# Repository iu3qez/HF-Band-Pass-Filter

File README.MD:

Preliminary version, please do not use.

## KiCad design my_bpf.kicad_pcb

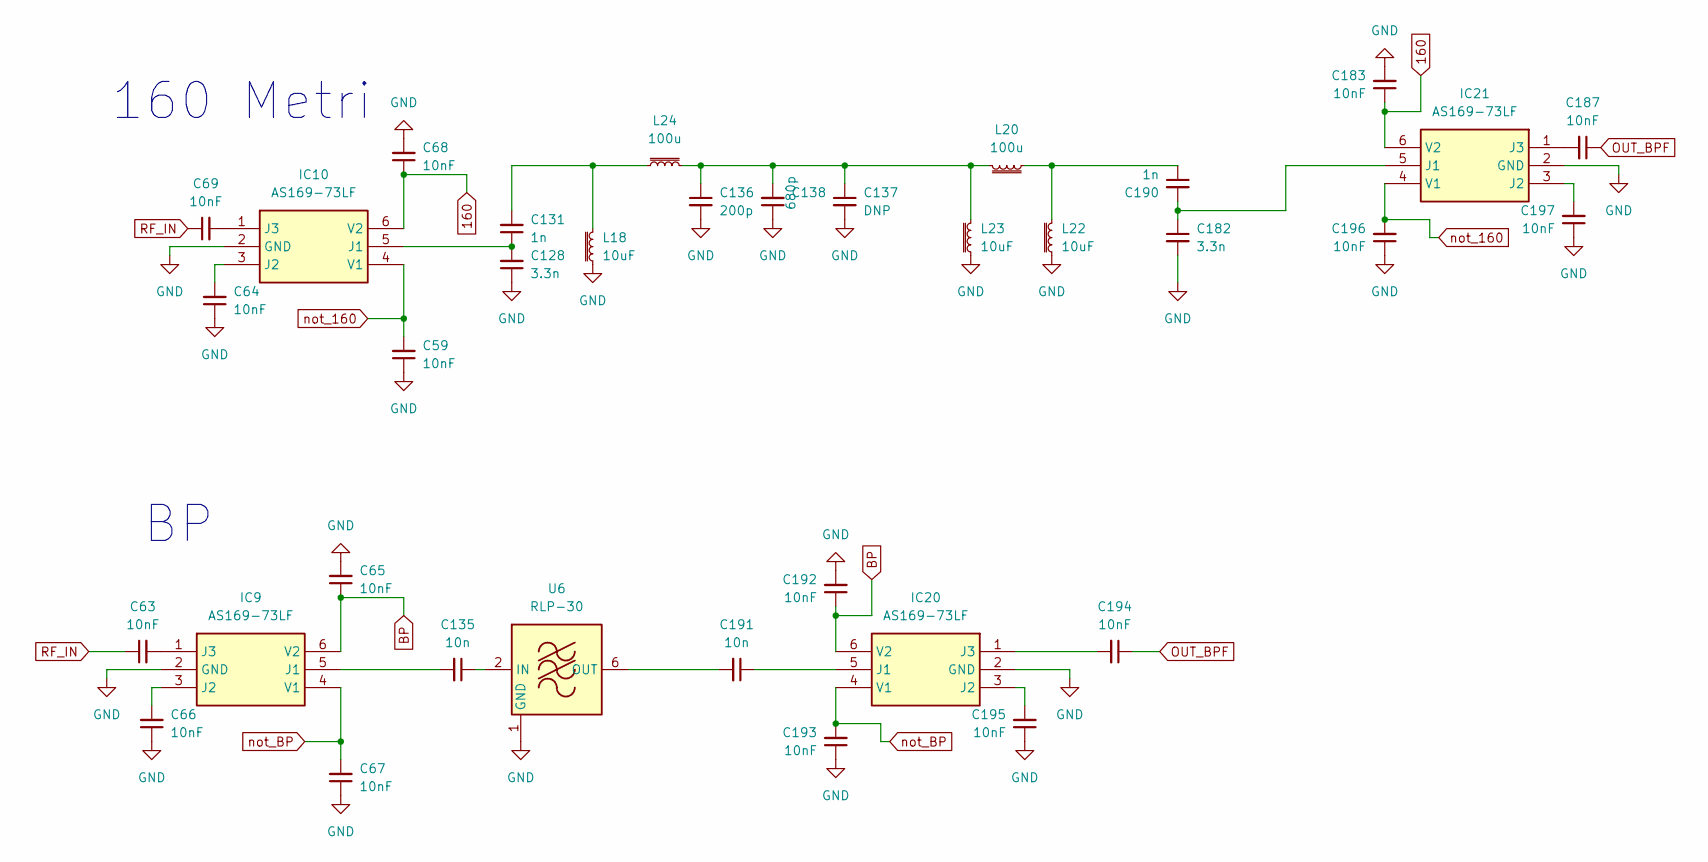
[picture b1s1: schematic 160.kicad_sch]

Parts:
C59, C63, C64, C65, C66, C67, C68, C69, C183, C187, C192, C193, C194, C195, C196, C197: 10nF; C_0603_1608Metric_Pad1.08x0.95mm_HandSolder
C128, C182: 3.3n; C_0603_1608Metric_Pad1.08x0.95mm_HandSolder
C131, C190: 1n; C_0603_1608Metric_Pad1.08x0.95mm_HandSolder
C135, C191: 10n; C_0603_1608Metric_Pad1.08x0.95mm_HandSolder
C136: 200p; C_0603_1608Metric_Pad1.08x0.95mm_HandSolder
C137: DNP; C_0603_1608Metric_Pad1.08x0.95mm_HandSolder
C138: 680p; C_0603_1608Metric_Pad1.08x0.95mm_HandSolder
IC9, IC10, IC20, IC21: AS169-73LF; SOT95P270X145-6N; Mouser Part Number 873-AS169-73LF
L18, L22, L23: 10uF; T37
L20, L24: 100u; T37
U6: RLP-30; Mini-Circuits_GP1212_LandPatternPL-176

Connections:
160: C68.1, C183.1, IC10.6 (V2), IC21.6 (V2); also elsewhere on the board
BP: C65.1, C192.1, IC9.6 (V2), IC20.6 (V2); also elsewhere on the board
GND: C59.1, C64.1, C65.2, C66.1, C67.1, C68.2, C128.1, C136.2, C137.2, C138.1, C182.2, C183.2, C192.2, C193.1, C195.1, C196.1, C197.1, IC9.2 (GND), IC10.2 (GND), IC20.2 (GND), IC21.2 (GND), L18.1, L22.1, L23.1, U6.1 (GND), U6.3 (GND), U6.4 (GND), U6.5 (GND), U6.7 (GND), U6.8 (GND); also elsewhere on the board
IN_BPF: C63.1, C69.1; also elsewhere on the board
unnamed: C131.2, L18.2, L24.1
unnamed: C136.1, C137.1, C138.2, L20.2, L23.2, L24.2
unnamed: C190.1, L20.1, L22.2
unnamed: C135.2, IC9.5 (J1)
unnamed: C66.2, IC9.3 (J2)
unnamed: C63.2, IC9.1 (J3)
unnamed: C128.2, C131.1, IC10.5 (J1)
unnamed: C64.2, IC10.3 (J2)
unnamed: C69.2, IC10.1 (J3)
unnamed: C191.1, IC20.5 (J1)
unnamed: C195.2, IC20.3 (J2)
unnamed: C194.2, IC20.1 (J3)
unnamed: C182.1, C190.2, IC21.5 (J1)
unnamed: C197.2, IC21.3 (J2)
unnamed: C187.2, IC21.1 (J3)
unnamed: C135.1, U6.2 (IN)
unnamed: C191.2, U6.6 (OUT)
OUT_BPF: C187.1, C194.1; also elsewhere on the board
not_160: C59.2, C196.2, IC10.4 (V1), IC21.4 (V1); also elsewhere on the board
not_BP: C67.2, C193.2, IC9.4 (V1), IC20.4 (V1); also elsewhere on the board

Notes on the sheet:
160 Metri

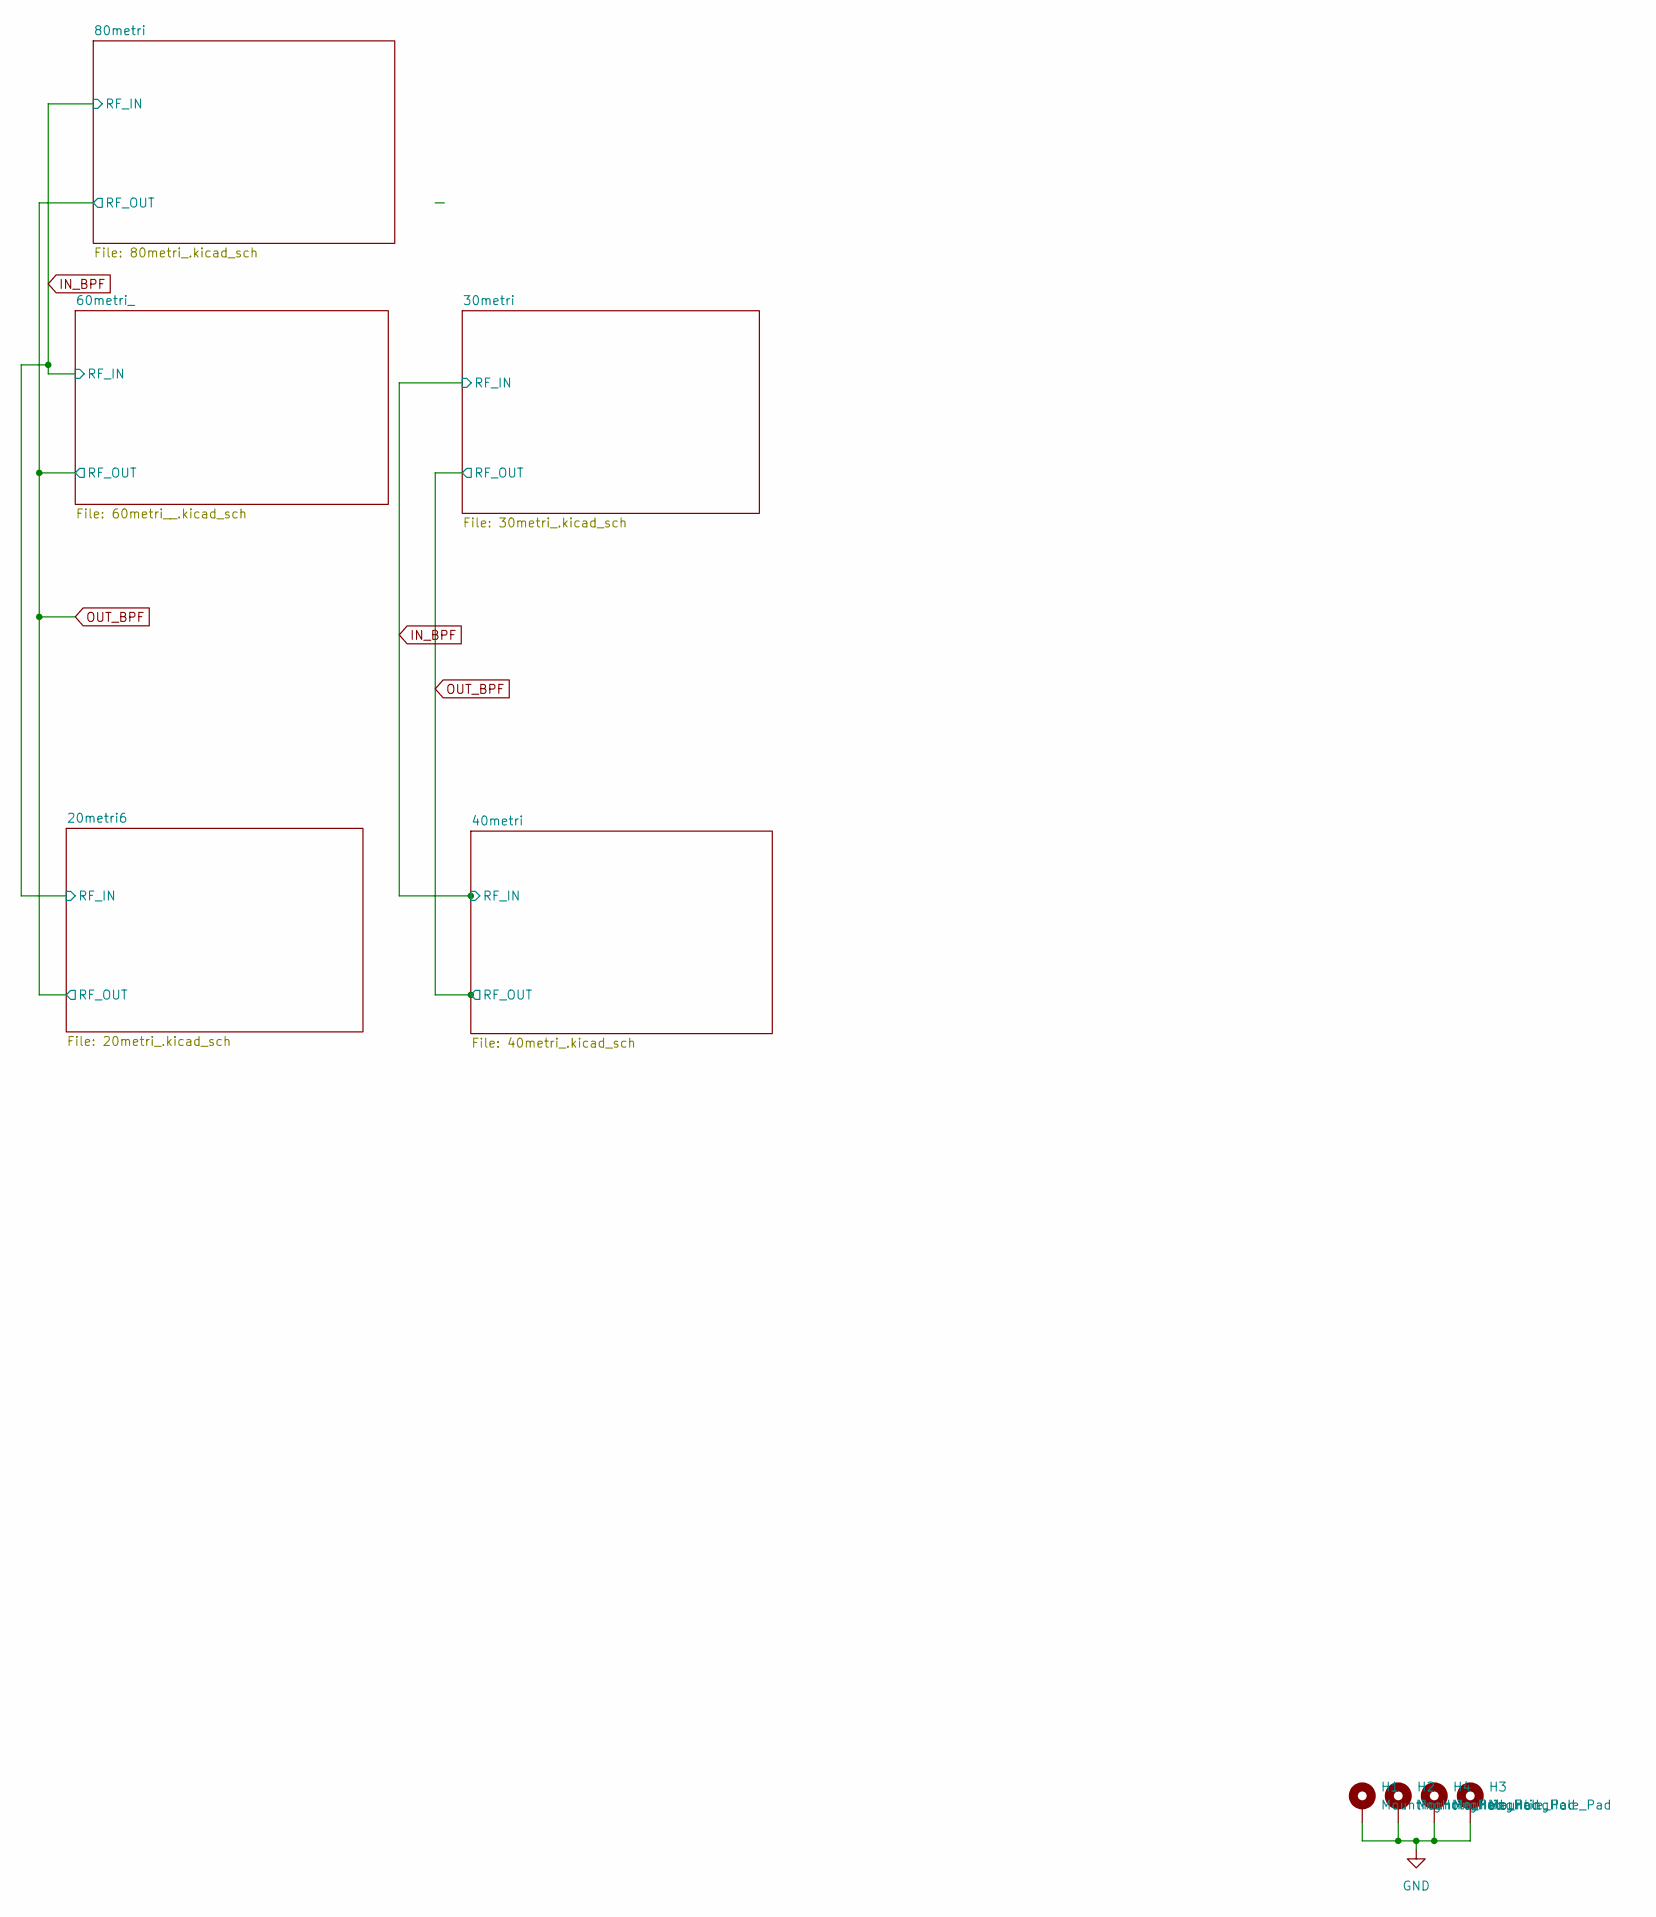
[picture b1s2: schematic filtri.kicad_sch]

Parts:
H1, H2, H3, H4: MountingHole_Pad; MountingHole_3.2mm_M3_Pad_TopBottom

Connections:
GND: H1.1, H2.1, H3.1, H4.1; also elsewhere on the board

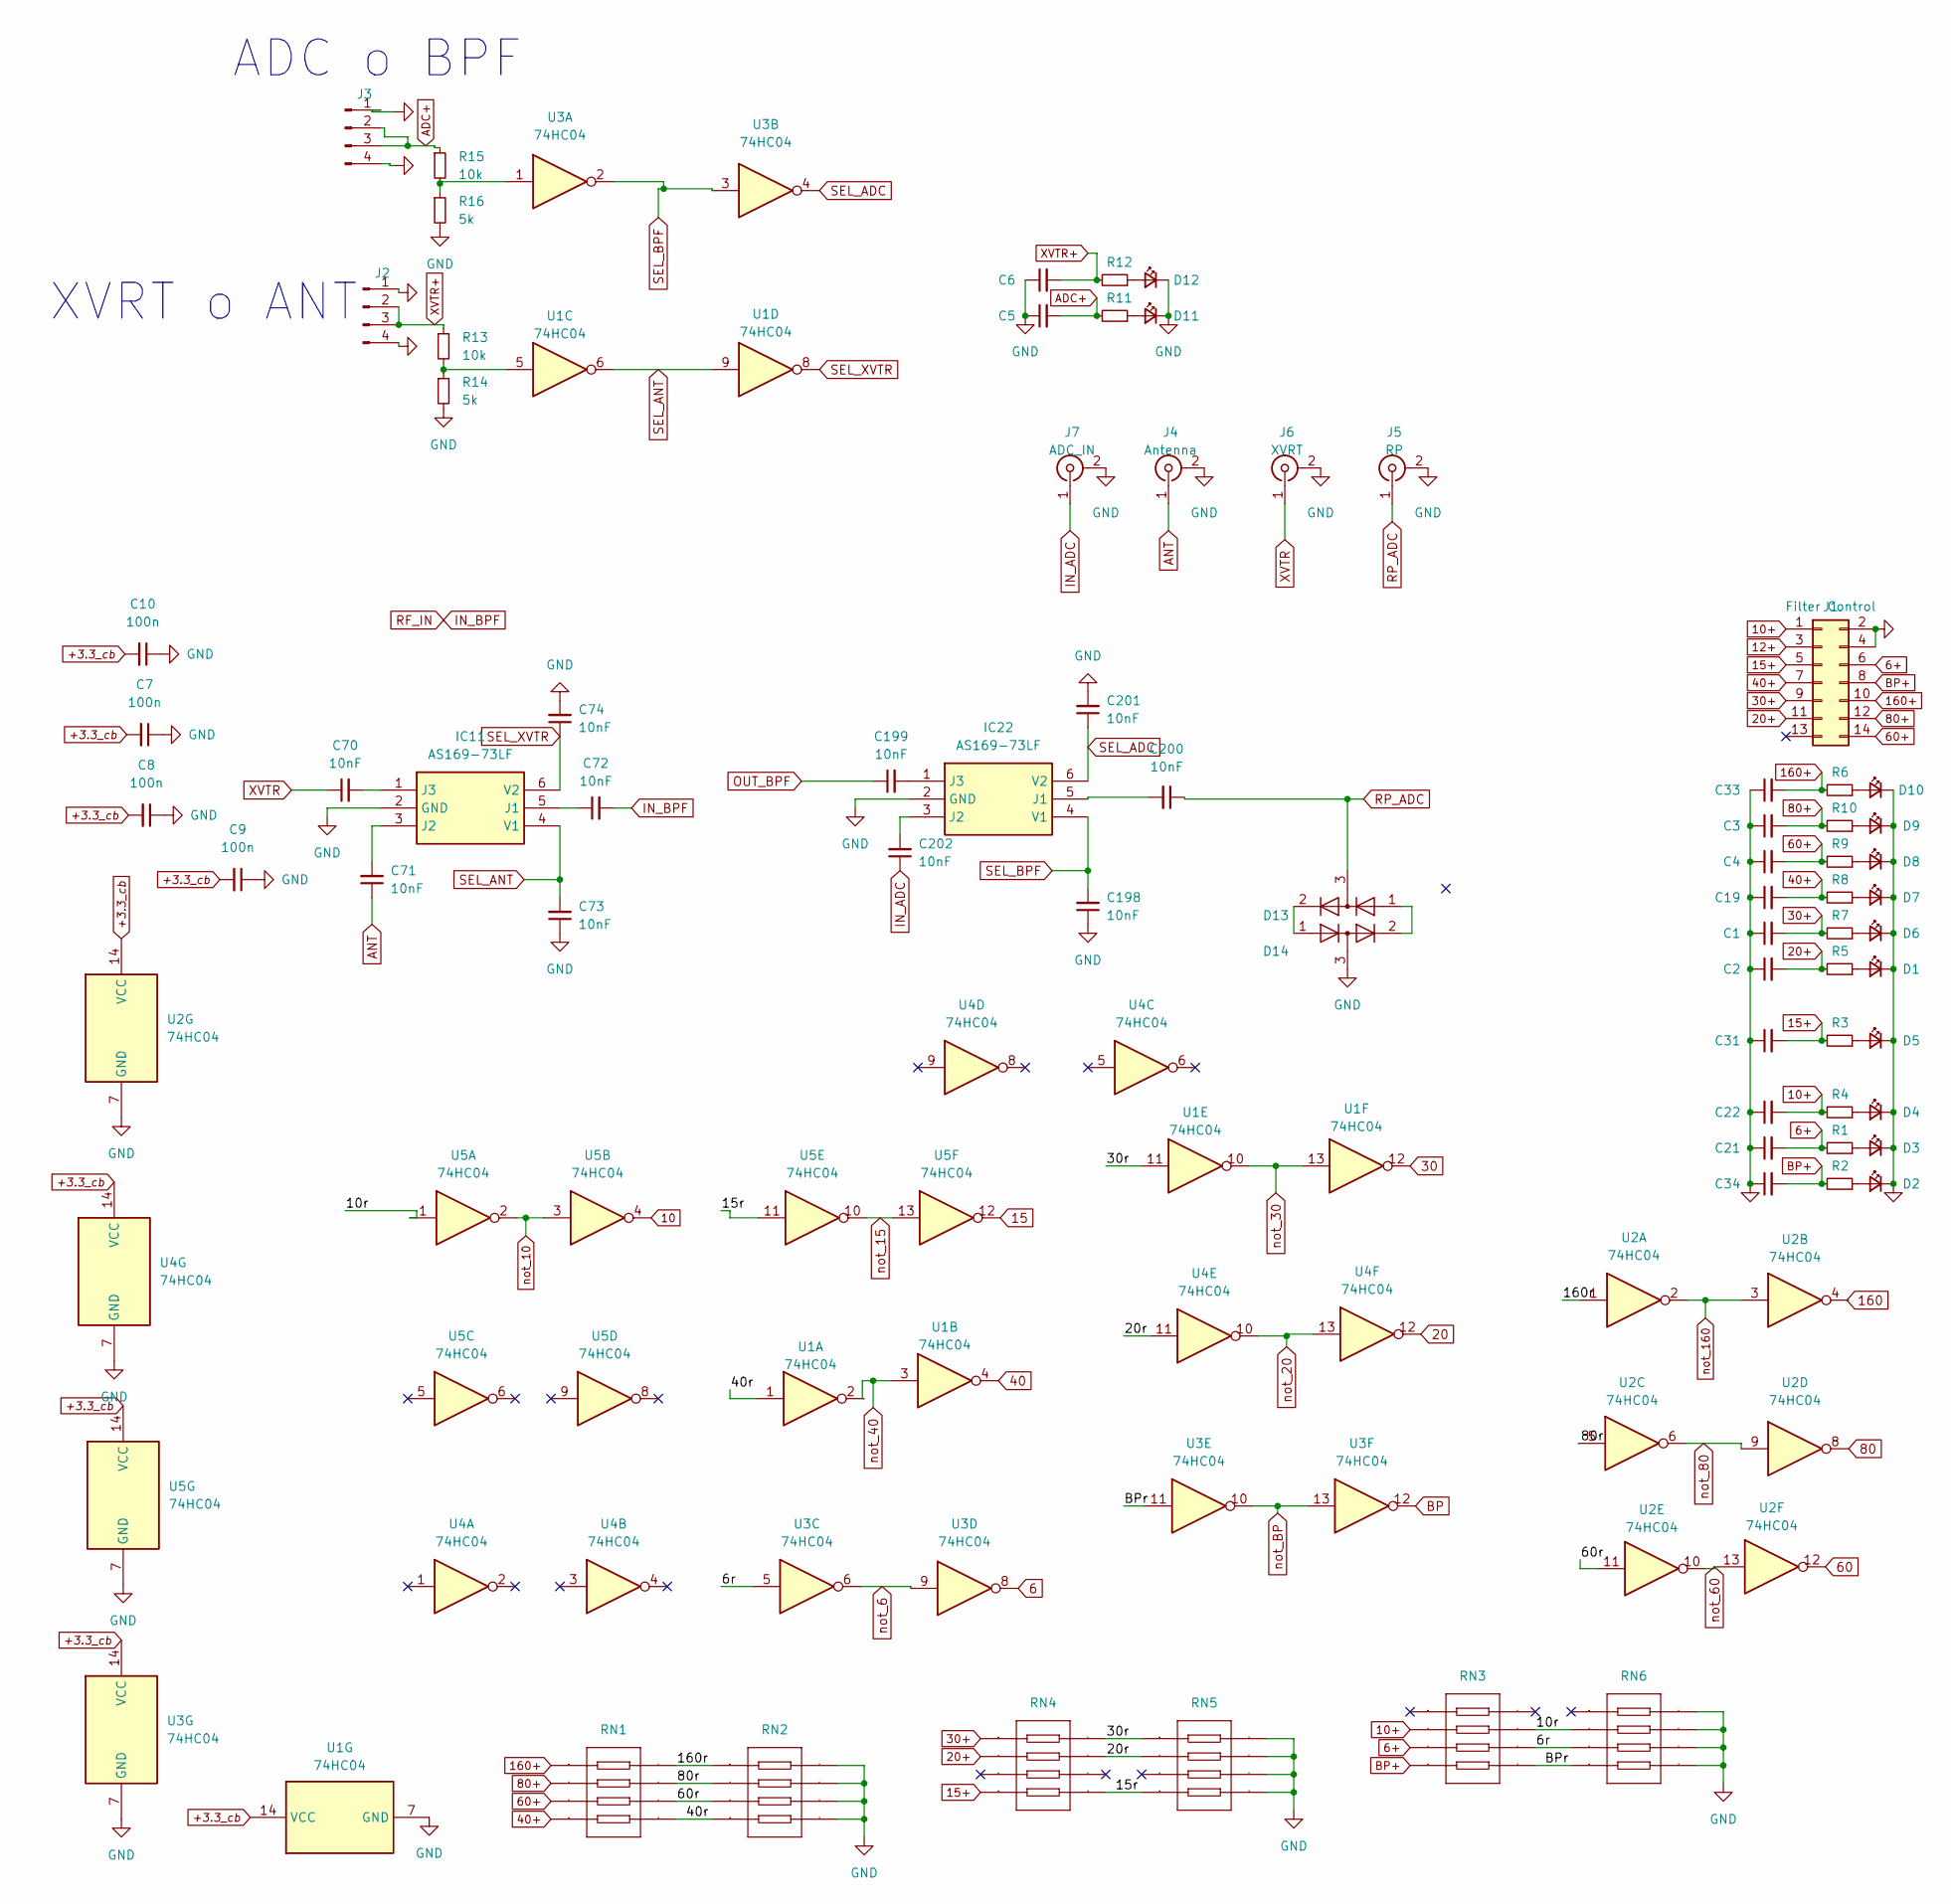
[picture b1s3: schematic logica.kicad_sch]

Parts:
C1, C2, C3, C4, C19, C21, C22, C31, C33, C34: C_Small; C_0603_1608Metric
C5, C6: 100n; C_0603_1608Metric
C7, C8, C9, C10: 100n; C_0603_1608Metric_Pad1.08x0.95mm_HandSolder
C70, C71, C72, C73, C74, C198, C199, C200, C201, C202: 10nF; C_0603_1608Metric_Pad1.08x0.95mm_HandSolder
D1, D2, D3, D4, D5, D6, D7, D8, D9, D10, D11, D12: LED_Small; LED_0603_1608Metric_Pad1.05x0.95mm_HandSolder
D13, D14: BAV99; SOT-23
IC11, IC22: AS169-73LF; SOT95P270X145-6N; Mouser Part Number 873-AS169-73LF
J1: Filter Control; PinHeader_2x07_P2.54mm_Horizontal
J2, J3: Conn_01x04_Male; PinHeader_1x04_P2.54mm_Vertical
J4: Antenna; SMA_Amphenol_901-144_Vertical
J5: RP; SMA_Amphenol_901-144_Vertical
J6: XVRT; SMA_Amphenol_901-144_Vertical
J7: ADC_IN; SMA_Amphenol_901-144_Vertical
R1, R2, R3, R4, R5, R6, R7, R8, R9, R10, R11, R12: R_Small; R_0603_1608Metric_Pad0.98x0.95mm_HandSolder
R13, R15: 10k; R_0603_1608Metric_Pad0.98x0.95mm_HandSolder
R14, R16: 5k; R_0603_1608Metric_Pad0.98x0.95mm_HandSolder
RN1, RN3, RN4: 10kΩ; RES-ARRAY-SMD_0603-8P-L3.2-W1.6-BL; Manufacturer Part 4D03WGJ0103T5E; LCSC Part Name 10kΩ ±5%
RN2, RN5, RN6: 5k; RES-ARRAY-SMD_0603-8P-L3.2-W1.6-BL; Manufacturer Part 4D03WGJ0103T5E; LCSC Part Name 10kΩ ±5%
U1, U2, U3, U4, U5: 74HC04; SOIC-14_3.9x8.7mm_P1.27mm

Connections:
6: U3.8; also elsewhere on the board
6+: C21.2, J1.6, R1.2, RN3.3
10: U5.4; also elsewhere on the board
10+: C22.2, J1.1, R4.2, RN3.2
12+: J1.3
15: U5.12; also elsewhere on the board
15+: C31.2, J1.5, R3.2, RN4.4
20: U4.12; also elsewhere on the board
20+: C2.2, J1.11, R5.2, RN4.2
30: U1.12; also elsewhere on the board
30+: C1.2, J1.9, R7.2, RN4.1
40: U1.4; also elsewhere on the board
40+: C19.2, J1.7, R8.2, RN1.4
60: U2.12; also elsewhere on the board
60+: C4.2, J1.14, R9.2, RN1.3
80: U2.8; also elsewhere on the board
80+: C3.2, J1.12, R10.2, RN1.2
160: U2.4; also elsewhere on the board
160+: C33.2, J1.10, R6.2, RN1.1
+3.3_cb: C7.2, C8.2, C9.2, C10.2, U1.14 (VCC), U2.14 (VCC), U3.14 (VCC), U4.14 (VCC), U5.14 (VCC)
/logica/6r: RN3.6, RN6.3, U3.5
/logica/10r: RN3.7, RN6.2, U5.1
/logica/15r: RN4.5, RN5.4, U5.11
/logica/20r: RN4.7, RN5.2, U4.11
/logica/30r: RN4.8, RN5.1, U1.11
/logica/40r: RN1.5, RN2.4, U1.1
/logica/60r: RN1.6, RN2.3, U2.11
/logica/80r: RN1.7, RN2.2, U2.5
/logica/160r: RN1.8, RN2.1, U2.1
/logica/BPr: RN3.5, RN6.4, U3.11
ADC+: C5.2, J3.2, J3.3, R11.2, R15.1
ANT: C71.1, J4.1 (In)
BP: U3.12; also elsewhere on the board
BP+: C34.2, J1.8, R2.2, RN3.4
GND: C1.1, C2.1, C3.1, C4.1, C5.1, C6.1, C7.1, C8.1, C9.1, C10.1, C19.1, C21.1, C22.1, C31.1, C33.1, C34.1, C73.1, C74.2, C198.1, C201.2, D1.1 (K), D2.1 (K), D3.1 (K), D4.1 (K), D5.1 (K), D6.1 (K), D7.1 (K), D8.1 (K), D9.1 (K), D10.1 (K), D11.1 (K), D12.1 (K), D14.3 (K), IC11.2 (GND), IC22.2 (GND), J1.2, J1.4, J2.1, J2.4, J3.1, J3.4, J4.2 (Ext), J5.2 (Ext), J6.2 (Ext), J7.2 (Ext), R14.2, R16.2, RN2.5, RN2.6, RN2.7, RN2.8, RN5.5, RN5.6, RN5.7, RN5.8, RN6.5, RN6.6, RN6.7, RN6.8, U1.7 (GND), U2.7 (GND), U3.7 (GND), U4.7 (GND), U5.7 (GND); also elsewhere on the board
IN_ADC: C202.1, J7.1 (In)
IN_BPF: C72.2; also elsewhere on the board
unnamed: D1.2 (A), R5.1
unnamed: D2.2 (A), R2.1
unnamed: D3.2 (A), R1.1
unnamed: D4.2 (A), R4.1
unnamed: D5.2 (A), R3.1
unnamed: D6.2 (A), R7.1
unnamed: D7.2 (A), R8.1
unnamed: D8.2 (A), R9.1
unnamed: D9.2 (A), R10.1
unnamed: D10.2 (A), R6.1
unnamed: D11.2 (A), R11.1
unnamed: D12.2 (A), R12.1
unnamed: D13.2 (A), D14.1 (K)
unnamed: D13.1 (K), D14.2 (A)
unnamed: C72.1, IC11.5 (J1)
unnamed: C71.2, IC11.3 (J2)
unnamed: C70.2, IC11.1 (J3)
unnamed: C200.2, IC22.5 (J1)
unnamed: C202.2, IC22.3 (J2)
unnamed: C199.2, IC22.1 (J3)
unnamed: R13.2, R14.1, U1.5
unnamed: R15.2, R16.1, U3.1
OUT_BPF: C199.1; also elsewhere on the board
RP_ADC: C200.1, D13.3 (K), J5.1 (In)
SEL_ADC: C201.1, IC22.6 (V2), U3.4
SEL_ANT: C73.2, IC11.4 (V1), U1.6, U1.9
SEL_BPF: C198.2, IC22.4 (V1), U3.2, U3.3
SEL_XVTR: C74.1, IC11.6 (V2), U1.8
XVTR: C70.1, J6.1 (In)
XVTR+: C6.2, J2.2, J2.3, R12.2, R13.1
not_6: U3.6, U3.9; also elsewhere on the board
not_10: U5.2, U5.3; also elsewhere on the board
not_15: U5.10, U5.13; also elsewhere on the board
not_20: U4.10, U4.13; also elsewhere on the board
not_30: U1.10, U1.13; also elsewhere on the board
not_40: U1.2, U1.3; also elsewhere on the board
not_60: U2.10, U2.13; also elsewhere on the board
not_80: U2.6, U2.9; also elsewhere on the board
not_160: U2.2, U2.3; also elsewhere on the board
not_BP: U3.10, U3.13; also elsewhere on the board

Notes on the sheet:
ADC o BPF
XVRT o ANT

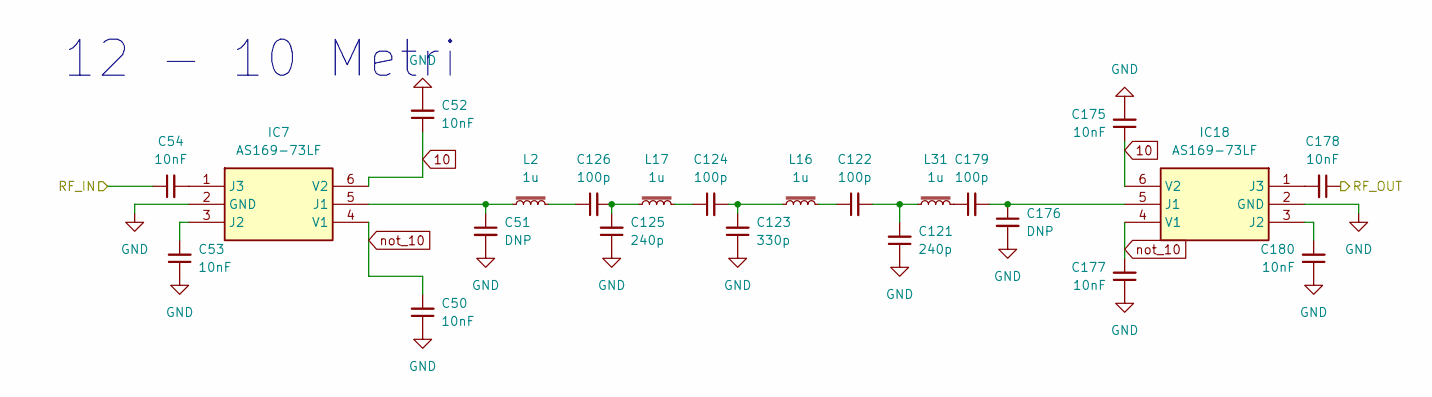
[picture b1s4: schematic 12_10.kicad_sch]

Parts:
C50, C52, C53, C54, C175, C177, C178, C180: 10nF; C_0603_1608Metric_Pad1.08x0.95mm_HandSolder
C51, C176: DNP; C_0805_2012Metric_Pad1.18x1.45mm_HandSolder
C121, C125: 240p; C_0805_2012Metric_Pad1.18x1.45mm_HandSolder
C122, C124, C126, C179: 100p; C_0805_2012Metric_Pad1.18x1.45mm_HandSolder
C123: 330p; C_0805_2012Metric_Pad1.18x1.45mm_HandSolder
IC7, IC18: AS169-73LF; SOT95P270X145-6N; Mouser Part Number 873-AS169-73LF
L2, L16, L17, L31: 1u; T37

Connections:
10: C52.1, C175.1, IC7.6 (V2), IC18.6 (V2); also elsewhere on the board
GND: C50.1, C51.2, C52.2, C53.1, C121.1, C123.1, C125.1, C175.2, C176.2, C177.1, C180.1, IC7.2 (GND), IC18.2 (GND); also elsewhere on the board
IN_BPF: C54.1; also elsewhere on the board
unnamed: C121.2, C122.2, L31.1
unnamed: C122.1, L16.2
unnamed: C123.2, C124.2, L16.1
unnamed: C124.1, L17.2
unnamed: C125.2, C126.2, L17.1
unnamed: C126.1, L2.2
unnamed: C179.1, L31.2
unnamed: C51.1, IC7.5 (J1), L2.1
unnamed: C53.2, IC7.3 (J2)
unnamed: C54.2, IC7.1 (J3)
unnamed: C176.1, C179.2, IC18.5 (J1)
unnamed: C180.2, IC18.3 (J2)
unnamed: C178.2, IC18.1 (J3)
OUT_BPF: C178.1; also elsewhere on the board
not_10: C50.2, C177.2, IC7.4 (V1), IC18.4 (V1); also elsewhere on the board

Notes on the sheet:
12 - 10 Metri

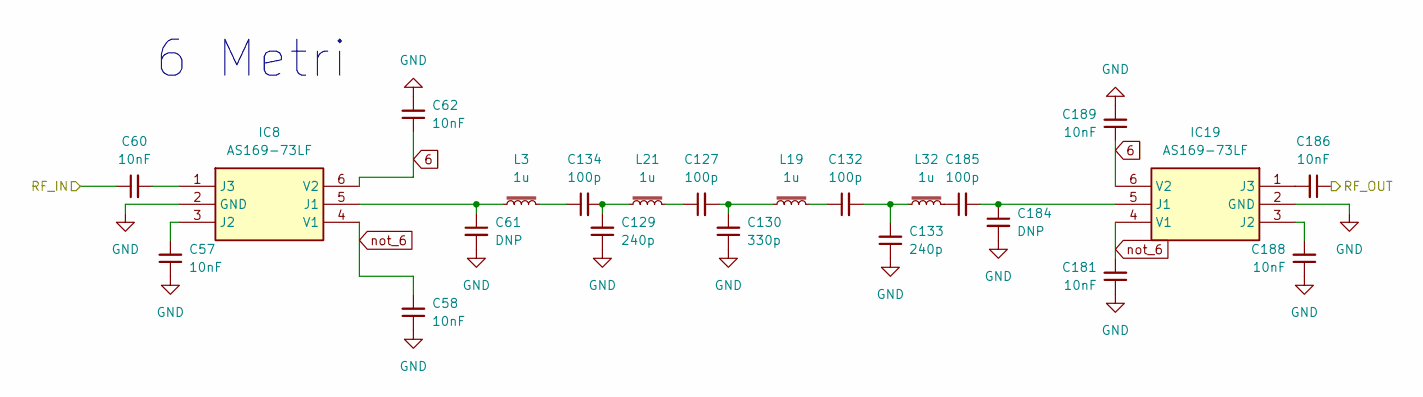
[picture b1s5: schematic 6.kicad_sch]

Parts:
C57, C58, C60, C62, C181, C186, C188, C189: 10nF; C_0603_1608Metric_Pad1.08x0.95mm_HandSolder
C61, C184: DNP; C_0805_2012Metric_Pad1.18x1.45mm_HandSolder
C127, C132, C134, C185: 100p; C_0805_2012Metric_Pad1.18x1.45mm_HandSolder
C129, C133: 240p; C_0805_2012Metric_Pad1.18x1.45mm_HandSolder
C130: 330p; C_0805_2012Metric_Pad1.18x1.45mm_HandSolder
IC8, IC19: AS169-73LF; SOT95P270X145-6N; Mouser Part Number 873-AS169-73LF
L3, L19, L21, L32: 1u; T37

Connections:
6: C62.1, C189.1, IC8.6 (V2), IC19.6 (V2); also elsewhere on the board
GND: C57.1, C58.1, C61.2, C62.2, C129.1, C130.1, C133.1, C181.1, C184.2, C188.1, C189.2, IC8.2 (GND), IC19.2 (GND); also elsewhere on the board
IN_BPF: C60.1; also elsewhere on the board
unnamed: C127.1, L21.2
unnamed: C127.2, C130.2, L19.1
unnamed: C129.2, C134.2, L21.1
unnamed: C132.1, L19.2
unnamed: C132.2, C133.2, L32.1
unnamed: C134.1, L3.2
unnamed: C185.1, L32.2
unnamed: C61.1, IC8.5 (J1), L3.1
unnamed: C57.2, IC8.3 (J2)
unnamed: C60.2, IC8.1 (J3)
unnamed: C184.1, C185.2, IC19.5 (J1)
unnamed: C188.2, IC19.3 (J2)
unnamed: C186.2, IC19.1 (J3)
OUT_BPF: C186.1; also elsewhere on the board
not_6: C58.2, C181.2, IC8.4 (V1), IC19.4 (V1); also elsewhere on the board

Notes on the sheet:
6 Metri

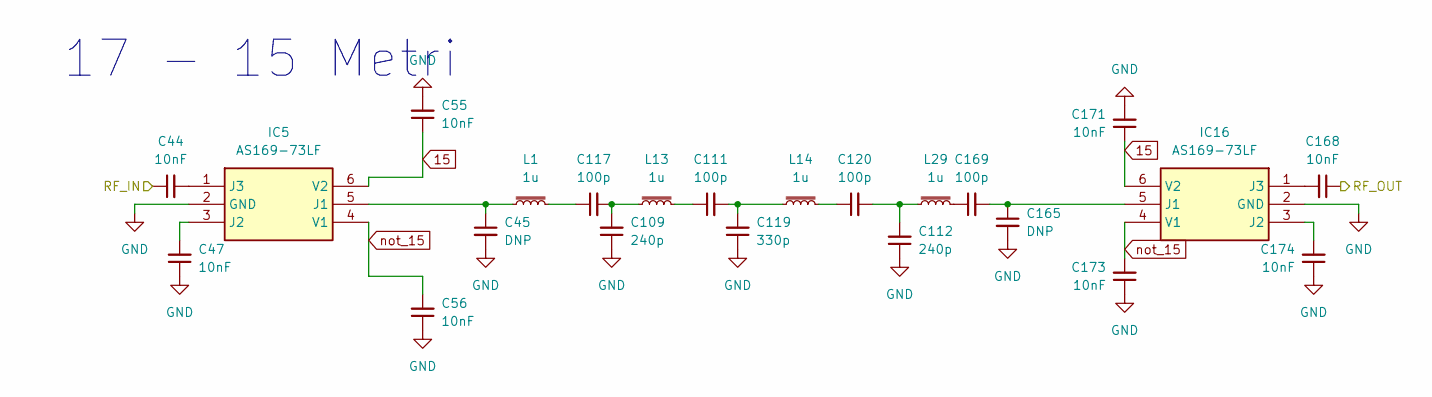
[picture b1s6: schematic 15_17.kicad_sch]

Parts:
C44, C47, C55, C56, C168, C171, C173, C174: 10nF; C_0603_1608Metric_Pad1.08x0.95mm_HandSolder
C45, C165: DNP; C_0805_2012Metric_Pad1.18x1.45mm_HandSolder
C109, C112: 240p; C_0805_2012Metric_Pad1.18x1.45mm_HandSolder
C111, C117, C120, C169: 100p; C_0805_2012Metric_Pad1.18x1.45mm_HandSolder
C119: 330p; C_0805_2012Metric_Pad1.18x1.45mm_HandSolder
IC5, IC16: AS169-73LF; SOT95P270X145-6N; Mouser Part Number 873-AS169-73LF
L1, L13, L14, L29: 1u; T37

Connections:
15: C55.1, C171.1, IC5.6 (V2), IC16.6 (V2); also elsewhere on the board
GND: C45.2, C47.1, C55.2, C56.1, C109.1, C112.1, C119.1, C165.2, C171.2, C173.1, C174.1, IC5.2 (GND), IC16.2 (GND); also elsewhere on the board
IN_BPF: C44.1; also elsewhere on the board
unnamed: C109.2, C117.2, L13.1
unnamed: C111.1, L13.2
unnamed: C111.2, C119.2, L14.1
unnamed: C112.2, C120.2, L29.1
unnamed: C117.1, L1.2
unnamed: C120.1, L14.2
unnamed: C169.1, L29.2
unnamed: C45.1, IC5.5 (J1), L1.1
unnamed: C47.2, IC5.3 (J2)
unnamed: C44.2, IC5.1 (J3)
unnamed: C165.1, C169.2, IC16.5 (J1)
unnamed: C174.2, IC16.3 (J2)
unnamed: C168.2, IC16.1 (J3)
OUT_BPF: C168.1; also elsewhere on the board
not_15: C56.2, C173.2, IC5.4 (V1), IC16.4 (V1); also elsewhere on the board

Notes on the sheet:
17 - 15 Metri

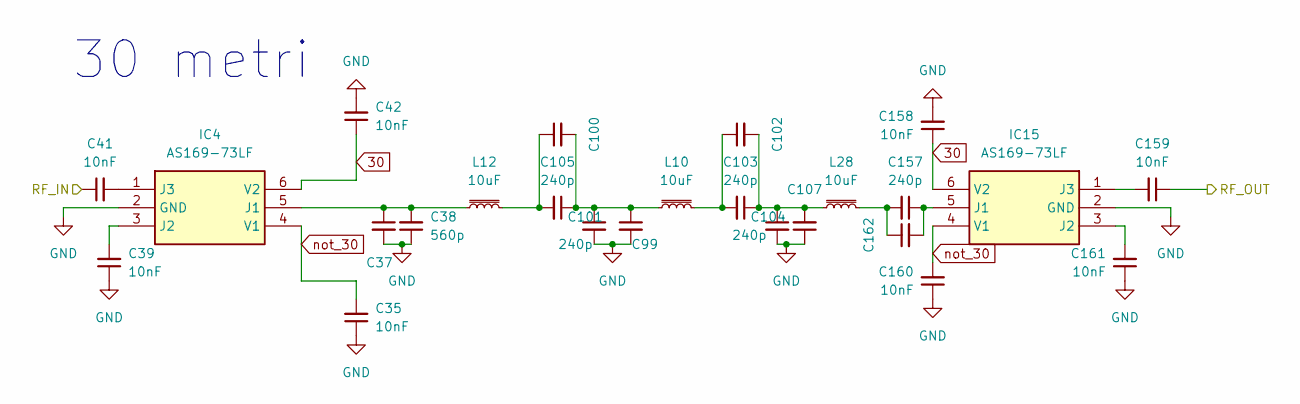
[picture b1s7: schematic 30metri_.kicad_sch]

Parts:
C35, C39, C41, C42, C158, C159, C160, C161: 10nF; C_0603_1608Metric_Pad1.08x0.95mm_HandSolder
C37, C99, C100, C102, C107, C162: DNP; C_0805_2012Metric_Pad1.18x1.45mm_HandSolder
C38: 560p; C_0805_2012Metric_Pad1.18x1.45mm_HandSolder
C101, C103, C104, C105, C157: 240p; C_0805_2012Metric_Pad1.18x1.45mm_HandSolder
IC4, IC15: AS169-73LF; SOT95P270X145-6N; Mouser Part Number 873-AS169-73LF
L10, L12, L28: 10uF; T37

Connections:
30: C42.1, C158.1, IC4.6 (V2), IC15.6 (V2); also elsewhere on the board
GND: C35.1, C37.2, C38.1, C39.1, C42.2, C99.2, C101.2, C104.2, C107.1, C158.2, C160.1, C161.1, IC4.2 (GND), IC15.2 (GND); also elsewhere on the board
IN_BPF: C41.1; also elsewhere on the board
unnamed: C100.1, C105.2, L12.2
unnamed: C99.1, C100.2, C101.1, C105.1, L10.1
unnamed: C102.1, C103.2, L10.2
unnamed: C102.2, C103.1, C104.1, C107.2, L28.1
unnamed: C157.2, C162.1, L28.2
unnamed: C37.1, C38.2, IC4.5 (J1), L12.1
unnamed: C39.2, IC4.3 (J2)
unnamed: C41.2, IC4.1 (J3)
unnamed: C157.1, C162.2, IC15.5 (J1)
unnamed: C161.2, IC15.3 (J2)
unnamed: C159.2, IC15.1 (J3)
OUT_BPF: C159.1; also elsewhere on the board
not_30: C35.2, C160.2, IC4.4 (V1), IC15.4 (V1); also elsewhere on the board

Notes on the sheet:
30 metri

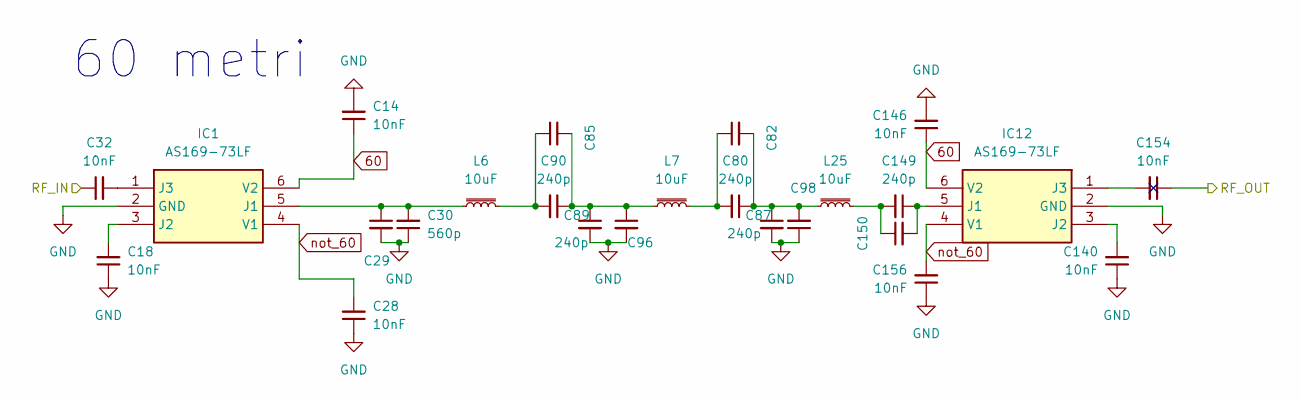
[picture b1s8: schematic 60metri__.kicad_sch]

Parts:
C14, C18, C28, C32, C140, C146, C154, C156: 10nF; C_0603_1608Metric_Pad1.08x0.95mm_HandSolder
C29, C82, C85, C96, C98, C150: DNP; C_0805_2012Metric_Pad1.18x1.45mm_HandSolder
C30: 560p; C_0805_2012Metric_Pad1.18x1.45mm_HandSolder
C80, C87, C89, C90, C149: 240p; C_0805_2012Metric_Pad1.18x1.45mm_HandSolder
IC1, IC12: AS169-73LF; SOT95P270X145-6N; Mouser Part Number 873-AS169-73LF
L6, L7, L25: 10uF; T37

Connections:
60: C14.1, C146.1, IC1.6 (V2), IC12.6 (V2); also elsewhere on the board
GND: C14.2, C18.1, C28.1, C29.2, C30.1, C87.2, C89.2, C96.2, C98.1, C140.1, C146.2, C156.1, IC1.2 (GND), IC12.2 (GND); also elsewhere on the board
IN_BPF: C32.1; also elsewhere on the board
unnamed: C80.1, C82.2, C87.1, C98.2, L25.1
unnamed: C80.2, C82.1, L7.2
unnamed: C85.1, C90.2, L6.2
unnamed: C85.2, C89.1, C90.1, C96.1, L7.1
unnamed: C149.2, C150.1, L25.2
unnamed: C29.1, C30.2, IC1.5 (J1), L6.1
unnamed: C18.2, IC1.3 (J2)
unnamed: C32.2, IC1.1 (J3)
unnamed: C149.1, C150.2, IC12.5 (J1)
unnamed: C140.2, IC12.3 (J2)
unnamed: C154.2, IC12.1 (J3)
OUT_BPF: C154.1; also elsewhere on the board
not_60: C28.2, C156.2, IC1.4 (V1), IC12.4 (V1); also elsewhere on the board

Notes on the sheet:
60 metri

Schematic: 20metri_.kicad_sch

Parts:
C36, C40, C46, C49, C163, C164, C166, C172: 10nF; C_0603_1608Metric_Pad1.08x0.95mm_HandSolder
C43, C108, C113, C116, C118, C167: DNP; C_0805_2012Metric_Pad1.18x1.45mm_HandSolder
C48: 560p; C_0805_2012Metric_Pad1.18x1.45mm_HandSolder
C106, C110, C114, C115, C170: 240p; C_0805_2012Metric_Pad1.18x1.45mm_HandSolder
IC6, IC17: AS169-73LF; SOT95P270X145-6N; Mouser Part Number 873-AS169-73LF
L11, L15, L30: 10uF; T37

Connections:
20: C40.1, C163.1, IC6.6 (V2), IC17.6 (V2); also elsewhere on the board
GND: C36.1, C40.2, C43.2, C46.1, C48.1, C113.1, C114.2, C115.2, C118.2, C163.2, C164.1, C166.1, IC6.2 (GND), IC17.2 (GND); also elsewhere on the board
IN_BPF: C49.1; also elsewhere on the board
unnamed: C106.1, C108.2, C113.2, C115.1, L30.1
unnamed: C106.2, C108.1, L15.2
unnamed: C110.1, C114.1, C116.2, C118.1, L15.1
unnamed: C110.2, C116.1, L11.2
unnamed: C167.1, C170.2, L30.2
unnamed: C43.1, C48.2, IC6.5 (J1), L11.1
unnamed: C36.2, IC6.3 (J2)
unnamed: C49.2, IC6.1 (J3)
unnamed: C167.2, C170.1, IC17.5 (J1)
unnamed: C166.2, IC17.3 (J2)
unnamed: C172.2, IC17.1 (J3)
OUT_BPF: C172.1; also elsewhere on the board
not_20: C46.2, C164.2, IC6.4 (V1), IC17.4 (V1); also elsewhere on the board

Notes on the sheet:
20 Metri

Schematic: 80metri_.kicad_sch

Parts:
C11, C12, C15, C16, C141, C143, C144, C145: 10nF; C_0603_1608Metric_Pad1.08x0.95mm_HandSolder
C13: 560p; C_0805_2012Metric_Pad1.18x1.45mm_HandSolder
C17, C75, C77, C78, C84, C142: DNP; C_0805_2012Metric_Pad1.18x1.45mm_HandSolder
C76, C79, C81, C83, C139: 240p; C_0805_2012Metric_Pad1.18x1.45mm_HandSolder
IC2, IC13: AS169-73LF; SOT95P270X145-6N; Mouser Part Number 873-AS169-73LF
L4, L5, L26: 10uF; T37

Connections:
80: C11.1, C143.1, IC2.6 (V2), IC13.6 (V2); also elsewhere on the board
GND: C11.2, C12.1, C13.1, C15.1, C17.2, C78.2, C81.2, C83.2, C84.1, C143.2, C144.1, C145.1, IC2.2 (GND), IC13.2 (GND); also elsewhere on the board
IN_BPF: C16.1; also elsewhere on the board
unnamed: C75.1, C76.2, L5.2
unnamed: C75.2, C76.1, C83.1, C84.2, L26.1
unnamed: C77.1, C79.2, L4.1
unnamed: C77.2, C78.1, C79.1, C81.1, L5.1
unnamed: C139.2, C142.1, L26.2
unnamed: C13.2, C17.1, IC2.5 (J1), L4.2
unnamed: C12.2, IC2.3 (J2)
unnamed: C16.2, IC2.1 (J3)
unnamed: C139.1, C142.2, IC13.5 (J1)
unnamed: C145.2, IC13.3 (J2)
unnamed: C141.2, IC13.1 (J3)
OUT_BPF: C141.1; also elsewhere on the board
not_80: C15.2, C144.2, IC2.4 (V1), IC13.4 (V1); also elsewhere on the board

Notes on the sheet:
80 Metri

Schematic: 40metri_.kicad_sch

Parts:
C20, C86, C92, C95, C97, C155: DNP; C_0805_2012Metric_Pad1.18x1.45mm_HandSolder
C23, C24, C25, C26, C147, C148, C151, C152: 10nF; C_0603_1608Metric_Pad1.08x0.95mm_HandSolder
C27: 560p; C_0805_2012Metric_Pad1.18x1.45mm_HandSolder
C88, C91, C93, C94, C153: 240p; C_0805_2012Metric_Pad1.18x1.45mm_HandSolder
IC3, IC14: AS169-73LF; SOT95P270X145-6N; Mouser Part Number 873-AS169-73LF
L8, L9, L27: 10uF; T37

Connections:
40: C24.1, C147.1, IC3.6 (V2), IC14.6 (V2); also elsewhere on the board
GND: C20.2, C23.1, C24.2, C26.1, C27.1, C86.2, C88.2, C92.1, C94.2, C147.2, C151.1, C152.1, IC3.2 (GND), IC14.2 (GND); also elsewhere on the board
IN_BPF: C25.1; also elsewhere on the board
unnamed: C86.1, C93.1, C94.1, C97.2, L9.1
unnamed: C88.1, C91.1, C92.2, C95.2, L27.1
unnamed: C91.2, C95.1, L9.2
unnamed: C93.2, C97.1, L8.2
unnamed: C153.2, C155.1, L27.2
unnamed: C20.1, C27.2, IC3.5 (J1), L8.1
unnamed: C23.2, IC3.3 (J2)
unnamed: C25.2, IC3.1 (J3)
unnamed: C153.1, C155.2, IC14.5 (J1)
unnamed: C152.2, IC14.3 (J2)
unnamed: C148.2, IC14.1 (J3)
OUT_BPF: C148.1; also elsewhere on the board
not_40: C26.2, C151.2, IC3.4 (V1), IC14.4 (V1); also elsewhere on the board

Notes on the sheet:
40 Metri

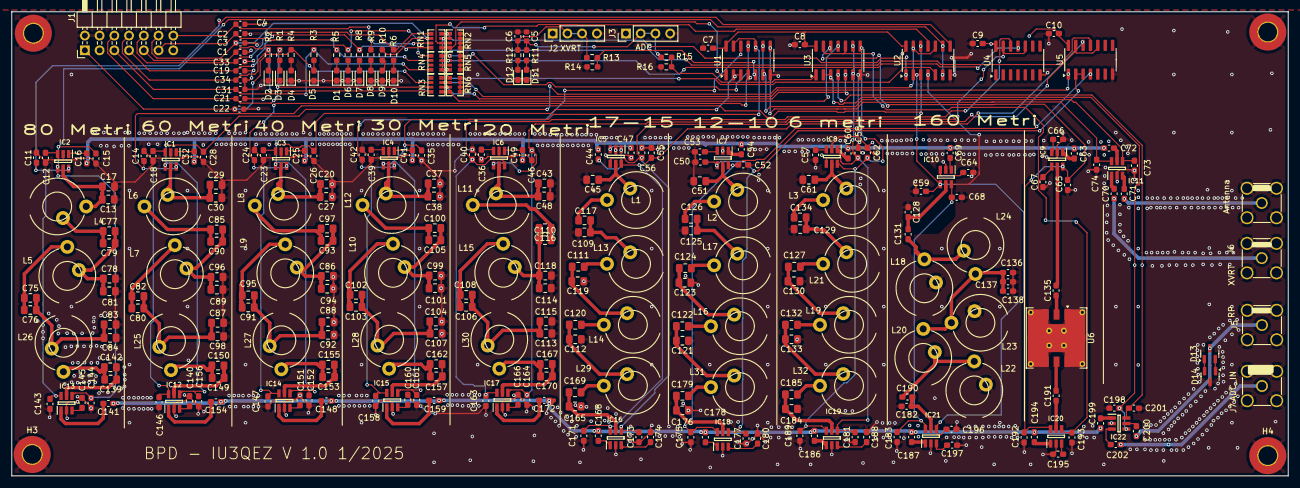
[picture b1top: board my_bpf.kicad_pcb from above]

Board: 4 copper layers, 220.0 x 80.0 mm, 309 parts (0 on the bottom side), 187 nets.

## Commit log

2025-04-30 Commit iniziale - ignore
2025-04-30 Redme
